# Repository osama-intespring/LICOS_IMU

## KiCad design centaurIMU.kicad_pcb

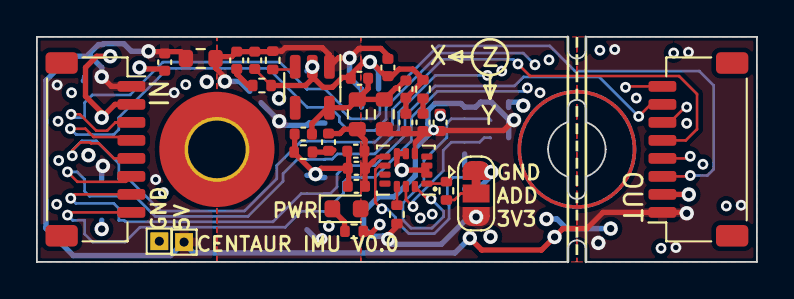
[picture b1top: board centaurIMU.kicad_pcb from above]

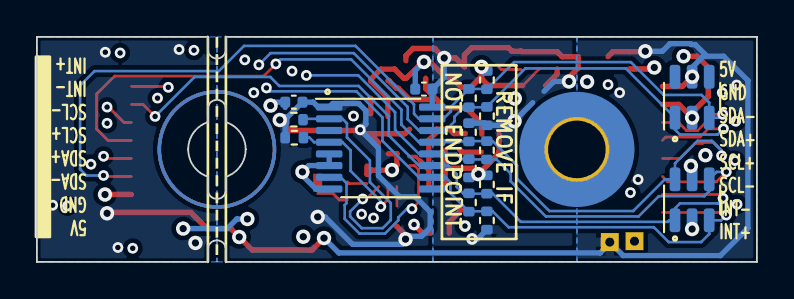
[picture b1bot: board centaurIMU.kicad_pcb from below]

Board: 4 copper layers, 40.0 x 12.5 mm, 50 parts (16 on the bottom side), 23 nets.

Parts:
C1, C2, C14, C501: 100nF 16V X7R ±10% 0402; C_0402_1005Metric
C3, C4, C5, C6, C8, C9, C11, C13: 1uF 25V X5R ±10% 0402; C_0402_1005Metric
C7, C10, C12, C15: 10uF 6.3V X5R ±20% 0402; C_0402_1005Metric
D1: LED 0603; LED_0603_1608Metric
FB1, FB2, FB3: TDK MPZ1608S101A (100Ω, 3A, 0603); R_0603_1608Metric
H1: MountingHole_Pad; MountingHole_3.2mm_M3_Pad_TopBottom
J1, J2: JST_SH_SM08B-SRSS-TB_1x08; JST_SH_SM08B-SRSS-TB_1x08-1MP_P1.00mm_Horizontal
JP1: LSB ADRESS; SolderJumper-3_P1.3mm_Open_RoundedPad1.0x1.5mm
NT1: NetTie_2; NetTie-2_SMD_Pad0.5mm
R1, R3, R4, R6, R7, R9: 600Ω; R_0402_1005Metric
R2, R5, R8: 120Ω; R_0402_1005Metric
R10, R12, R13: 2R; R_0402_1005Metric
R11, R15, R16, R17, R18: 10kΩ; R_0402_1005Metric
R14: 2k2Ω; R_0402_1005Metric
TP3, TP4: TestPoint; TestPoint_THTPad_1.0x1.0mm_Drill0.5mm
U1: PCA9616PW; TSSOP-16_4.4x5mm_P0.65mm
U2: LD39015M33R; SOT-23-5
U3: ASM330LHH; LGA-14_3x2.5mm_P0.5mm_LayoutBorder3x4y
U4, U5: USBLC6-4SC6; SOT-23-6

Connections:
+3V3: C4.1, C5.1, C8.1, FB1.1, FB3.1, U2.5 (OUT)
+5V: C11.1, FB2.1, J1.1, J2.1, TP3.1, U4.5 (VBUS), U5.5 (VBUS)
/D_INT_N: J1.7, J2.7, R5.1, R6.2, U1.11 (DINTM), U4.1 (I/O1)
/D_INT_P: J1.8, J2.8, R4.1, R5.2, U1.10 (DINTP), U4.3 (I/O2)
/D_SCL_N: J1.6, J2.6, R2.1, R3.2, U1.12 (DSCLM), U4.4 (I/O3)
/D_SCL_P: J1.5, J2.5, R1.1, R2.2, U1.13 (DSCLP), U4.6 (I/O4)
/D_SDA_N: J1.3, J2.3, R8.1, R9.2, U1.15 (DSDAM), U5.3 (I/O2)
/D_SDA_P: J1.4, J2.4, R7.1, R8.2, U1.14 (DSDAP), U5.1 (I/O1)
/IMU/IMU_ADDRESS: R15.1, U3.1 (SDO/SA0)
/IMU/IMU_CS: R18.1, U3.12 (CS)
/IMU/add: JP1.2 (C), NT1.2, R15.2
/IMU/π - Filter 1Mhz 0.5A3/Vout: C9.1, C10.1, C14.2, C15.2, FB3.2, U3.8 (VDD)
/IMU_INT: U1.7 (INT), U3.9 (INT2)
/IMU_SCL: R17.1, U1.4 (SCL), U3.13 (SCL)
/IMU_SDA: R16.1, U1.2 (SDA), U3.14 (SDA)
GND: C1.1, C2.1, C3.2, C4.2, C5.2, C7.2, C8.2, C10.2, C11.2, C12.2, C14.1, C15.1, C501.1, J1.2, J2.2, JP1.1 (A), NT1.1, R3.1, R6.1, R9.1, R10.2, R12.2, R13.2, R14.2, TP4.1, U1.5 (NPIDET), U1.6 (NREADY), U1.8 (V_{SS}), U2.2 (GND), U3.2 (SDX), U3.3 (SCX), U3.6 (GND), U3.7 (GND), U4.2 (GND), U5.2 (GND)
unnamed: C6.2, R10.1
unnamed: C9.2, R13.1
unnamed: C13.2, R12.1
unnamed: D1.1 (K), R14.1
unnamed: R11.2, U2.3 (EN)
VBUS: C1.2, C3.1, C12.1, C13.1, FB2.2, R1.2, R4.2, R7.2, R11.1, U1.16 (V_{DD(B)}), U2.1 (IN)
VDDA: C2.2, C6.1, C7.1, C501.2, FB1.2, JP1.3 (B), R16.2, R17.2, R18.2, U1.1 (V_{DD(A)}), U3.5 (VDDIO)

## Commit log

2025-10-29 Initial commit: imported centaurIMU files
2025-10-29 Changed names of files
